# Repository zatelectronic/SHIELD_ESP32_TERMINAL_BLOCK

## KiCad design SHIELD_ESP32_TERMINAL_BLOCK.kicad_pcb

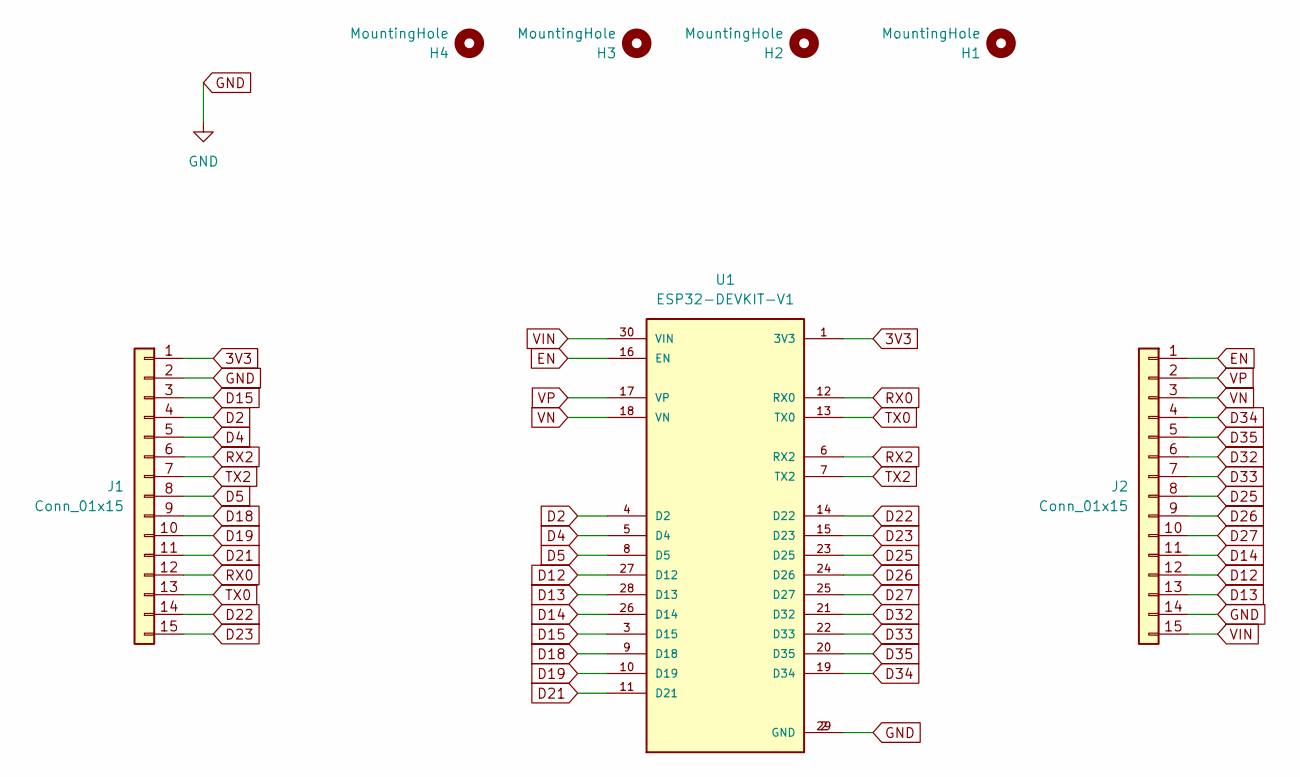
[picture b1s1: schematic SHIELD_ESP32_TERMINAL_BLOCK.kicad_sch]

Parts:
H1, H2, H3, H4: MountingHole; MountingHole_3.2mm_M3_ISO14580
J1, J2: Conn_01x15; TerminalBlock_MaiXu_MX126-5.0-15P_1x15_P5.00mm
U1: ESP32-DEVKIT-V1; MODULE_ESP32_DEVKIT_V1; PARTREV N/A

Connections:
3V3: J1.1, U1.1 (3V3)
D2: J1.4, U1.4 (D2)
D4: J1.5, U1.5 (D4)
D5: J1.8, U1.8 (D5)
D12: J2.12, U1.27 (D12)
D13: J2.13, U1.28 (D13)
D14: J2.11, U1.26 (D14)
D15: J1.3, U1.3 (D15)
D18: J1.9, U1.9 (D18)
D19: J1.10, U1.10 (D19)
D21: J1.11, U1.11 (D21)
D22: J1.14, U1.14 (D22)
D23: J1.15, U1.15 (D23)
D25: J2.8, U1.23 (D25)
D26: J2.9, U1.24 (D26)
D27: J2.10, U1.25 (D27)
D32: J2.6, U1.21 (D32)
D33: J2.7, U1.22 (D33)
D34: J2.4, U1.19 (D34)
D35: J2.5, U1.20 (D35)
EN: J2.1, U1.16 (EN)
GND: J1.2, J2.14, U1.2 (GND), U1.29 (GND)
RX0: J1.12, U1.12 (RX0)
RX2: J1.6, U1.6 (RX2)
TX0: J1.13, U1.13 (TX0)
TX2: J1.7, U1.7 (TX2)
VIN: J2.15, U1.30 (VIN)
VN: J2.3, U1.18 (VN)
VP: J2.2, U1.17 (VP)

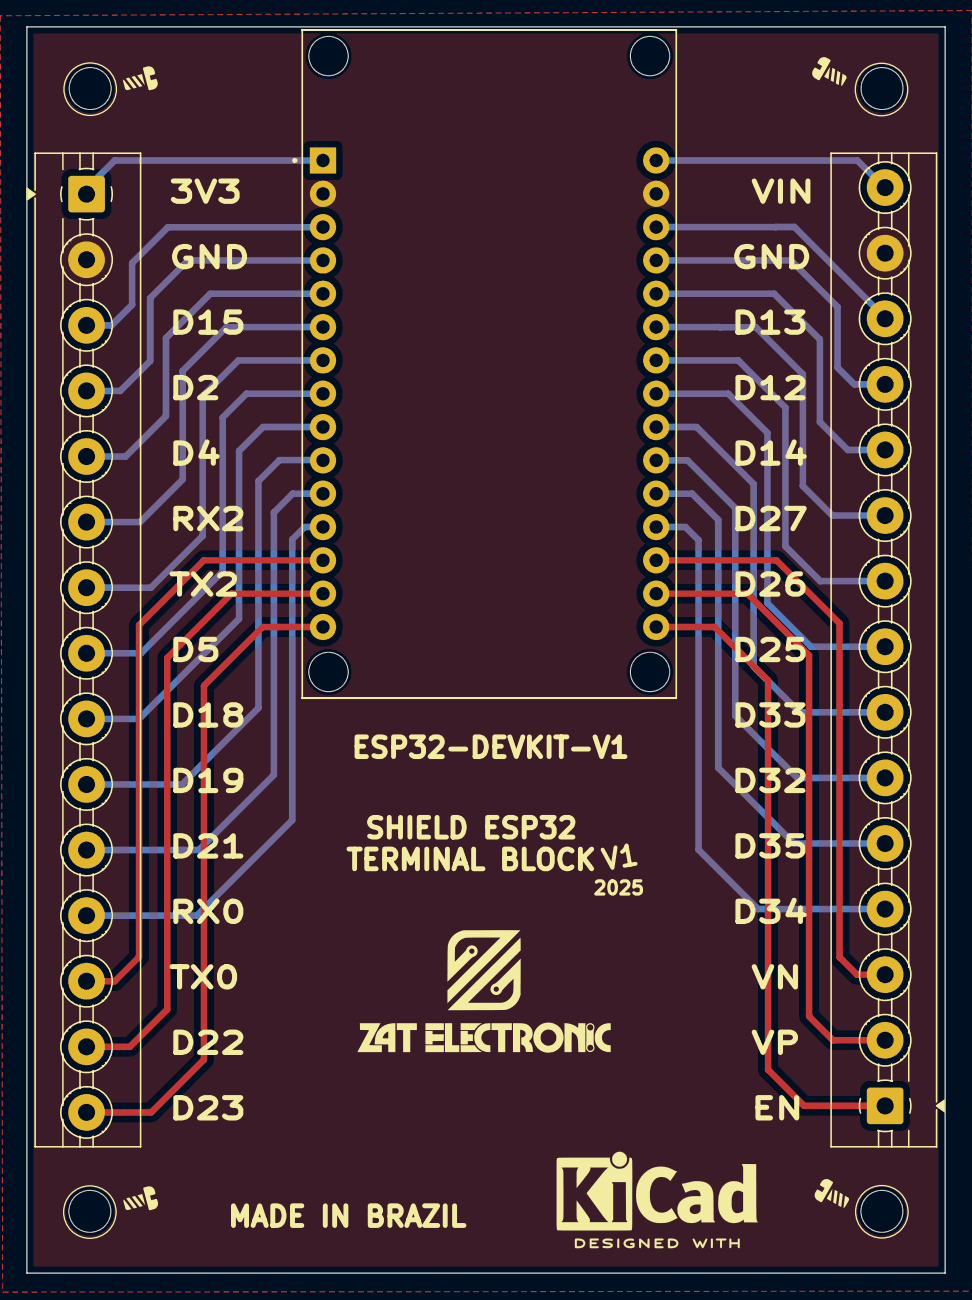
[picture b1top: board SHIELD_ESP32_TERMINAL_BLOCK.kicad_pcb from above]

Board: 2 copper layers, 70.0 x 95.0 mm, 7 parts (0 on the bottom side), 29 nets.
